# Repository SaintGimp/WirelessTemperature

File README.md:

# Wireless temperature sensors

This project is documented via a series of posts on my blog, [starting here](https://saintgimp.org/2016/07/10/building-a-wireless-temperature-sensor-network-part-1/).

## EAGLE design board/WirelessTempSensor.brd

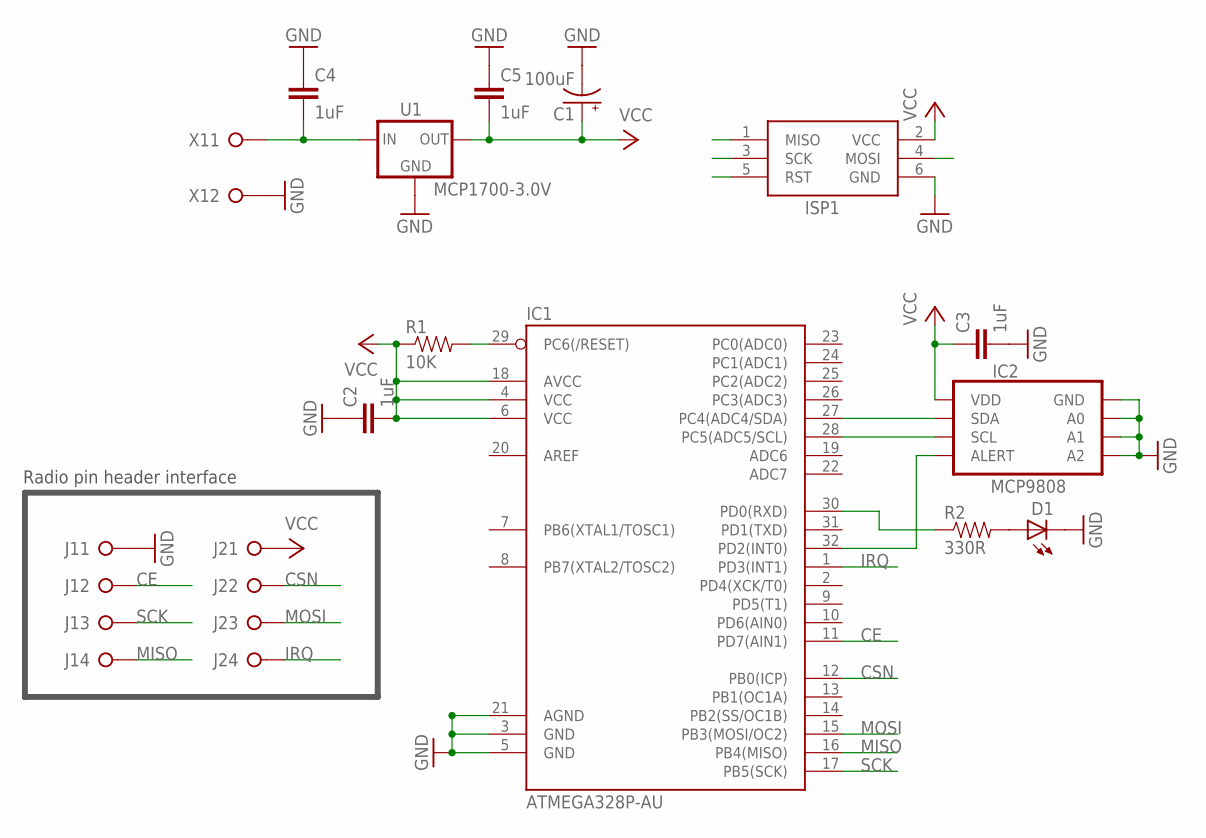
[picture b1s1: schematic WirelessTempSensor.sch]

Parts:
C1: 100uF; CAP-POL-2.5-6
C2, C3, C4, C5: 1uF; CAPACITOR-0805
D1: LED-0805
IC1: ATMEGA328P-AU; QFP32-08
IC2: MCP9808; MSOP8-0.65-3X3MM
ISP1: ICSP-HEADER-6; ICSP-HEADER
J1, J2: PINHD-1X4; 1X04
R1: 10K; RESISTOR-0805
R2: 330R; RESISTOR-0805
U1: MCP1700-3.0V; SOT-23-3
X1: SCREW-TERM-2

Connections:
ALERT: IC1.32 (PD2(INT0)), IC2.3 (ALERT)
CE: IC1.11 (PD7(AIN1)), J1.2
CSN: IC1.12 (PB0(ICP)), J2.2
GND: C1.-, C2.1, C3.2, C4.1, C5.1, D1.2 (C), IC1.3 (GND), IC1.5 (GND), IC1.21 (AGND), IC2.4 (GND), IC2.5 (A2), IC2.6 (A1), IC2.7 (A0), ISP1.6 (GND), J1.1, U1.1 (GND), X1.2
IRQ: IC1.1 (PD3(INT1)), J2.4
MISO: IC1.16 (PB4(MISO)), ISP1.1 (MISO), J1.4
MOSI: IC1.15 (PB3(MOSI/OC2)), ISP1.4 (MOSI), J2.3
unnamed: IC1.30 (PD0(RXD)), R2.1
unnamed: D1.1 (A), R2.2
RST: IC1.29 (PC6(/RESET)), ISP1.5 (RST), R1.2
SCK: IC1.17 (PB5(SCK)), ISP1.3 (SCK), J1.3
SCL: IC1.28 (PC5(ADC5/SCL)), IC2.2 (SCL)
SDA: IC1.27 (PC4(ADC4/SDA)), IC2.1 (SDA)
VCC: C1.+, C2.2, C3.1, C5.2, IC1.4 (VCC), IC1.6 (VCC), IC1.18 (AVCC), IC2.8 (VDD), ISP1.2 (VCC), J2.1, R1.1, U1.2 (OUT)
VIN: C4.2, U1.3 (IN), X1.1

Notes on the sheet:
Radio pin header interface

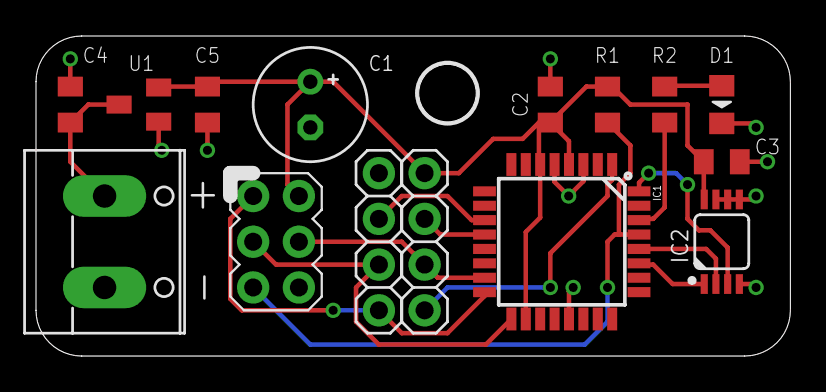
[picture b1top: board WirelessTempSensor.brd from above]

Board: 2 copper layers, 41.9 x 17.8 mm, 16 parts (0 on the bottom side), 15 nets.

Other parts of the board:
U$3: MOUNTING-HOLE-3.2MM

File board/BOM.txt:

Part Value         Device         Package          PartNumber          
C1   100uF         CAP-POL-2.5-6  CAP-POL-2.5-6    generic, 10V
C2   1uF           CAPACITOR-0805 CAPACITOR-0805   generic, X7R-type preferred
C3   1uF           CAPACITOR-0805 CAPACITOR-0805   generic, X7R-type preferred    
C4   1uF           CAPACITOR-0805 CAPACITOR-0805   generic, X7R-type preferred
C5   1uF           CAPACITOR-0805 CAPACITOR-0805   generic, X7R-type preferred
D1   LED-0805      LED-0805       LED-0805         LS R976-NR-1 (or equivalent)                     
IC1  ATMEGA328P-AU ATMEGA328P-AU  QFP32-08         ATMEGA328P-AU                     
IC2  MCP9808       MCP9808        MSOP8-0.65-3X3MM MCP9808T-E/MS                     
R1   10K           RESISTOR-0805  RESISTOR-0805    generic                     
R2   330R          RESISTOR-0805  RESISTOR-0805    generic                     
U1   MCP1700-3.0V  MCP1700-SOT23  SOT-23-3         MCP1700T-3002E/TT

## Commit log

2016-03-07 Initial sensor code
2016-03-24 Add logger and base code
2016-03-24 Add Eagle files for sensor board
2016-03-24 Add license and readme
2016-04-07 Use webhooks to log data to Phant
2016-04-07 Remove old logger
2016-07-11 Clean up schematic a bit
2016-07-18 Add comments to id.ino
2017-03-03 Improvements to base station code
2018-02-03 Add Fusion 360 export of base station case
2018-02-03 Add BOM for sensor board
2018-05-14 Change extended fuse to match new AVRDude behavior
2018-08-28 Update BOM with more common value for R2
2019-04-20 Move base station code to Particle Workbench
2021-10-01 Attempt to fix app hang
2021-10-01 Use JSON writer instead of abusing string objects
